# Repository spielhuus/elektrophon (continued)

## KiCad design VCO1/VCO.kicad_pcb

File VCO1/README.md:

# VCO1

This is a basic VCO designed by Thomas Henry. There are no special features, but it is a solid mixer.

Lorem ipsum dolor sit amet, consectetuer adipiscing elit. Aenean commodo ligula eget dolor. Aenean massa. Cum sociis natoque
penatibus et magnis dis parturient montes, nascetur ridiculus mus. Donec quam felis, ultricies nec, pellentesque eu, pretium quis, sem. Nulla consequat massa quis enim. Donec pede justo, fringilla vel, aliquet nec, vulputate eget, arcu. In enim justo, rhoncus ut, imperdiet a, venenatis vitae, justo. Nullam dictum felis eu pede mollis pretium. Integer tincidunt. Cras dapibus. Vivamus elementum semper nisi. Aenean vulputate eleifend tellus. Aenean leo ligula, porttitor eu, consequat vitae, eleifend ac, enim. Aliquam lorem ante, dapibus in, viverra quis, feugiat a, tellus. Phasellus viverra nulla ut metus varius laoreet. Quisque rutrum. Aenean imperdiet. Etiam ultricies nisi vel augue. Curabitur ullamcorper ultricies nisi. Nam eget dui. Etiam rhoncus. Maecenas tempus, tellus eget condimentum rhoncus, sem quam semper libero, sit amet adipiscing sem neque 

sed ipsum. Nam quam nunc, blandit vel, luctus pulvinar, hendrerit id, lorem. Maecenas nec odio et ante tincidunt tempus. Donec vitae sapien ut libero venenatis faucibus. Nullam quis ante. Etiam sit amet orci eget eros faucibus tincidunt. Duis leo. Sed fringilla mauris sit amet nibh. Donec sodales sagittis magna. Sed consequat, leo eget bibendum sodales, augue velit cursus nunc, Lorem ipsum dolor sit amet, consectetuer adipiscing elit. Aenean commodo ligula eget dolor. Aenean massa. Cum sociis natoque penatibus et magnis dis parturient montes, nascetur ridiculus mus. Donec quam felis, ultricies nec, pellentesque eu, pretium quis, sem. Nulla consequat massa quis enim. Donec pede justo, fringilla vel, aliquet nec, vulputate eget, arcu. In enim justo, rhoncus ut, imperdiet a, venenatis vitae, justo. Nullam dictum felis eu pede mollis pretium. Integer tincidunt. Cras dapibus. Vivamus elementum semper nisi. Aenean vulputate eleifend tellus. Aenean leo ligula, porttitor eu, consequat vitae, eleifend ac, enim. Aliquam lorem ante, dapibus in, viverra quis, feugiat a, tellus. Phasellus viverra nulla ut metus varius laoreet. Quisque rutrum. Aenean imperdiet. Etiam ultricies nisi vel augue. 

Curabitur ullamcorper ultricies nisi. Nam eget dui. Etiam rhoncus. Maecenas tempus, tellus eget condimentum rhoncus, sem quam semper libero, sit amet adipiscing sem neque sed ipsum. Nam quam nunc, blandit vel, luctus pulvinar, hendrerit id, lorem. Maecenas nec odio et ante tincidunt tempus. Donec vitae sapien ut libero venenatis faucibus. Nullam quis ante. Etiam sit amet orci eget eros faucibus tincidunt. Duis leo. Sed fringilla mauris sit amet nibh. Donec sodales sagittis magna. Sed consequat, leo eget bibendum sodales, augue velit cursus nunc - [BOM](BOM.csv) adipiscing sem neque sed ipsum. Nam quam nunc, blandit vel, luctus pulvinar, hendrerit id, lorem. Maecenas nec odio et ante tincidunt tempus. Donec vitae sapien ut libero venenatis faucibus. Nullam quis ante. Etiam sit amet orci eget eros faucibus tincidunt. Duis leo. Sed fringilla mauris sit amet nibh. Donec sodales sagittis magna. Sed consequat, leo eget bibendum sodales, augue velit cursus nun

## links

1) [Thomas Henry: VCO1](http://birthofasynth.com/Thomas_Henry/Pages/VCO-1.html)

---

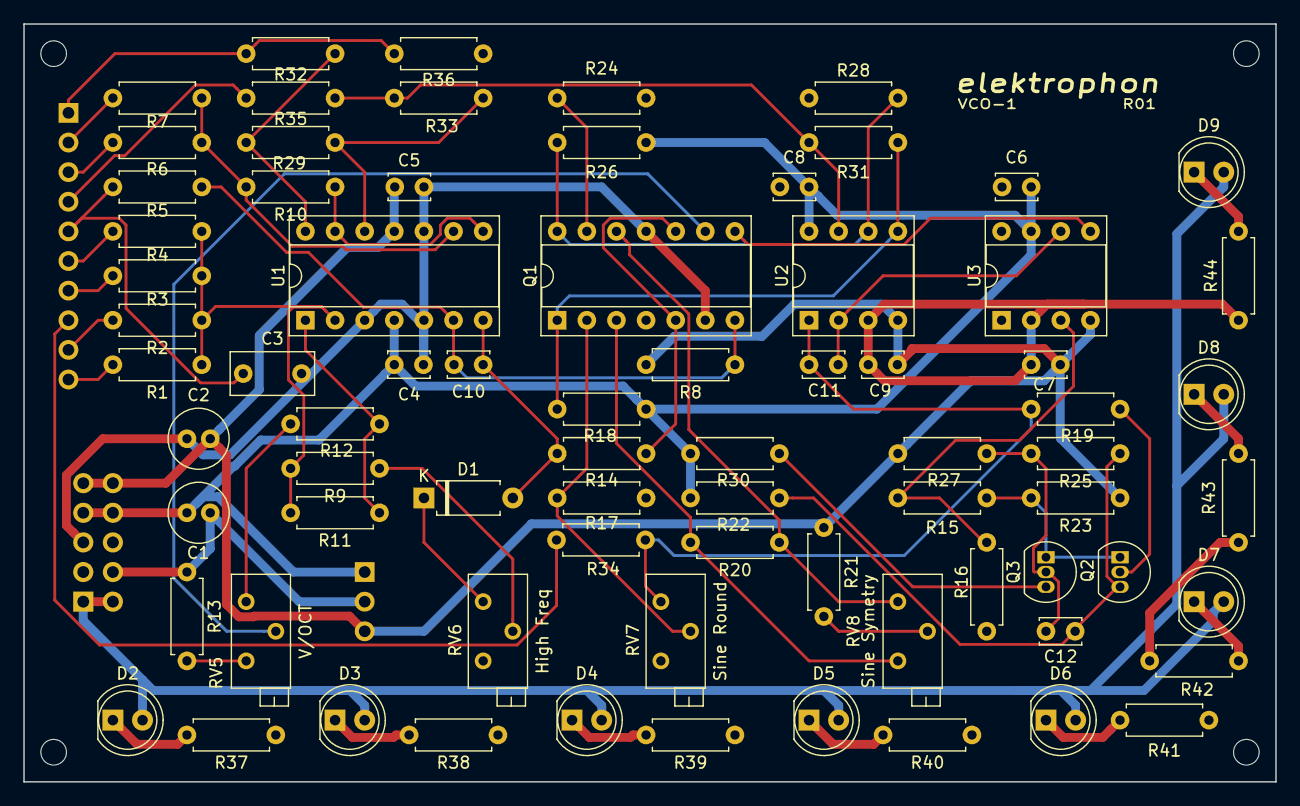
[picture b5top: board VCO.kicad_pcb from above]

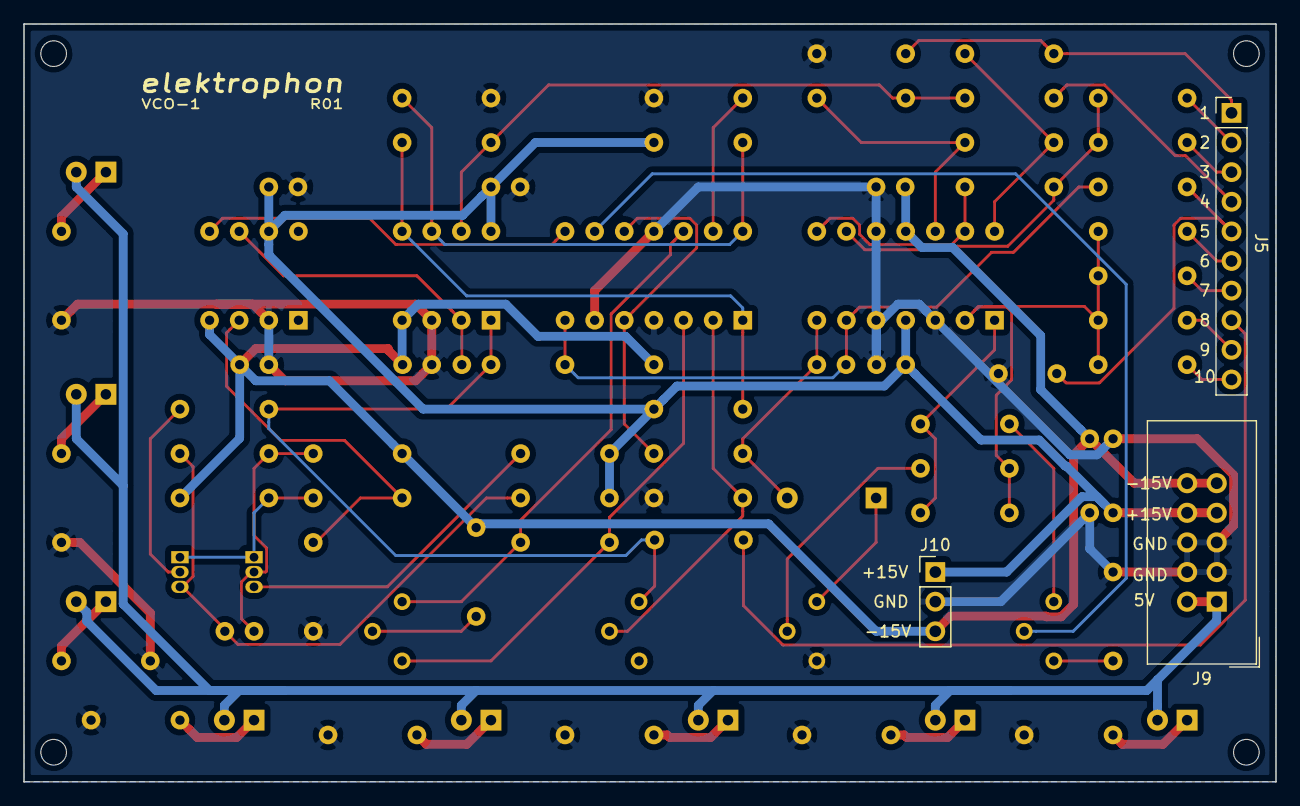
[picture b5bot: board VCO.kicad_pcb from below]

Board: 2 copper layers, 107.3 x 65.0 mm, 78 parts (3 on the bottom side), 53 nets.

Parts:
C1, C2: 10u; C_Radial_D5.0mm_H11.0mm_P2.00mm
C3: 0.22u; C_Rect_L7.0mm_W3.5mm_P5.00mm
C4, C5, C6, C7, C8, C9: 0.01u; C_Disc_D3.4mm_W2.1mm_P2.50mm
C10: 1n; C_Disc_D3.4mm_W2.1mm_P2.50mm
C11: 0.001u; C_Disc_D3.4mm_W2.1mm_P2.50mm
C12: 47p; C_Disc_D3.4mm_W2.1mm_P2.50mm
D1: D; D_A-405_P7.62mm_Horizontal
D2, D3, D4, D5, D6, D7, D8, D9: LED; LED_D5.0mm_FlatTop
J5: PANEL; PinHeader_1x10_P2.54mm_Vertical
J9: POWER; IDC-Header_2x05_P2.54mm_Vertical
J10: Panel Power; PinHeader_1x03_P2.54mm_Vertical
Q1: THAT340; DIP-14_W7.62mm_Socket
Q2, Q3: 2N3904; TO-92_Inline
R1, R2, R4, R6, R15, R27: 100k; R_Axial_DIN0207_L6.3mm_D2.5mm_P7.62mm_Horizontal
R3: 3M3; R_Axial_DIN0207_L6.3mm_D2.5mm_P7.62mm_Horizontal
R5: 1M; R_Axial_DIN0207_L6.3mm_D2.5mm_P7.62mm_Horizontal
R7: 330k; R_Axial_DIN0207_L6.3mm_D2.5mm_P7.62mm_Horizontal
R8: 1M5; R_Axial_DIN0207_L6.3mm_D2.5mm_P7.62mm_Horizontal
R9, R29: 2M2; R_Axial_DIN0207_L6.3mm_D2.5mm_P7.62mm_Horizontal
R10: 150k; R_Axial_DIN0207_L6.3mm_D2.5mm_P7.62mm_Horizontal
R11: 2k; R_Axial_DIN0207_L6.3mm_D2.5mm_P7.62mm_Horizontal
R12: 47; R_Axial_DIN0207_L6.3mm_D2.5mm_P7.62mm_Horizontal
R13: 820; R_Axial_DIN0207_L6.3mm_D2.5mm_P7.62mm_Horizontal
R14: 22k; R_Axial_DIN0207_L6.3mm_D2.5mm_P7.62mm_Horizontal
R16, R18, R22, R23, R24: 10k; R_Axial_DIN0207_L6.3mm_D2.5mm_P7.62mm_Horizontal
R17, R26, R28, R33: 2.2k; R_Axial_DIN0207_L6.3mm_D2.5mm_P7.62mm_Horizontal
R19: 27k; R_Axial_DIN0207_L6.3mm_D2.5mm_P7.62mm_Horizontal
R20: 390; R_Axial_DIN0207_L6.3mm_D2.5mm_P7.62mm_Horizontal
R21, R25: 18k; R_Axial_DIN0207_L6.3mm_D2.5mm_P7.62mm_Horizontal
R30: 5.1k; R_Axial_DIN0207_L6.3mm_D2.5mm_P7.62mm_Horizontal
R31: 12k; R_Axial_DIN0207_L6.3mm_D2.5mm_P7.62mm_Horizontal
R32, R36: 3k; R_Axial_DIN0207_L6.3mm_D2.5mm_P7.62mm_Horizontal
R34, R35, R37, R38, R39, R40, R41, R42, R43, R44: 1k; R_Axial_DIN0207_L6.3mm_D2.5mm_P7.62mm_Horizontal
RV5: 100 - V/OCT Trim; Potentiometer_Bourns_3296Z_Horizontal
RV6: 100k - High Freq Trim; Potentiometer_Bourns_3296Z_Horizontal
RV7: 100k - Sine Round Trim; Potentiometer_Bourns_3296Z_Horizontal
RV8: 50k - Sine Symetrie Trim; Potentiometer_Bourns_3296Z_Horizontal
U1: TL074; DIP-14_W7.62mm_Socket
U2: TL072; DIP-8_W7.62mm_Socket
U3: CA3080; DIP-8_W7.62mm_Socket

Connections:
+5V: D2.2, D3.2, D4.2, D5.2, D6.2, D7.2, D8.2, D9.2, J9.1, J9.2
+15V: C1.1, C4.1, C6.1, C8.1, J9.7, J9.8, J10.1, R18.2, R22.1, R24.2, R30.2, U1.4, U2.8, U3.7
-15V: C2.2, C5.2, C7.2, C9.2, J9.9, J9.10, J10.3, R8.2, R21.1, R23.1, R27.1, U1.11, U2.4, U3.4
/CV: J5.10, R1.2
/Coarse: J5.9, R2.2
/EXP_FM: J5.6, R4.2
/FINE: J5.7, R3.2
/INITIAL: J5.2, R7.2
/LIN_FM: C3.1, J5.5, R5.2
/PWM: J5.3, R6.2
/Pulse: J5.1, R32.1, R36.2
/Sine: J5.4, R35.1
/Triangle: J5.8, R34.1
GND: C1.2, C2.1, C3.2, C4.2, C5.1, C6.2, C7.1, C8.2, C9.1, J9.3, J9.4, J9.5, J9.6, J10.2, Q1.4, Q1.6, Q1.11, R13.1, R16.1, R17.1, R26.1, R28.1, R36.1, R37.1, R38.1, R39.1, R40.1, R41.1, R42.1, R43.1, R44.1, RV6.3, U1.3, U1.5, U1.10, U2.3, U3.2
unnamed: C10.1, D1.2, R14.1, U1.7
unnamed: C10.2, Q1.7, R5.1, R8.1, U1.6
unnamed: C11.1, R19.1, R34.2, RV7.1, U2.1
unnamed: C11.2, U2.2, U3.6
unnamed: C12.1, Q3.2, R25.2, R27.2
unnamed: C12.2, Q2.3, R22.2, R25.1
unnamed: D1.1, RV6.1
unnamed: D2.1, R37.2
unnamed: D3.1, R38.2
unnamed: D4.1, R39.2
unnamed: D5.1, R40.2
unnamed: D6.1, R41.2
unnamed: D7.1, R42.2
unnamed: D8.1, R43.2
unnamed: D9.1, R44.2
unnamed: Q1.1, R18.1, R31.2, U2.5
unnamed: Q1.2, R17.2, RV7.2
unnamed: Q1.3, R20.2, RV8.3
unnamed: Q1.8, U3.5
unnamed: Q1.9, RV5.2
unnamed: Q1.5, Q1.10, R14.2
unnamed: Q1.12, R20.1, RV8.1
unnamed: Q1.13, R26.2
unnamed: Q1.14, R24.1, R28.2, U2.6
unnamed: Q2.1, Q3.1, R15.2, R23.2
unnamed: Q2.2, R19.2
unnamed: Q3.3, R30.1
unnamed: R1.1, R2.1, R3.1, R4.1, R9.2, R11.2, U1.2
unnamed: R9.1, RV6.2
unnamed: R10.1, U1.8, U1.13
unnamed: R6.1, R7.1, R10.2, U1.9
unnamed: R11.1, R12.2, U1.1
unnamed: R12.1, RV5.1
unnamed: R13.2, RV5.3
unnamed: R15.1, R16.2, U3.3
unnamed: R21.2, RV8.2
unnamed: R29.1, R32.2, U1.14
unnamed: R29.2, R33.1, U1.12
unnamed: R31.1, R33.2, R35.2, U2.7

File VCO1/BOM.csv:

Reference, Quantity, Value, Footprint, Datasheet
C10 ,1,"1n","Capacitor_THT:C_Disc_D3.4mm_W2.1mm_P2.50mm","~"
C11 ,1,"0.001u","Capacitor_THT:C_Disc_D3.4mm_W2.1mm_P2.50mm","~"
C12 ,1,"47p","Capacitor_THT:C_Disc_D3.4mm_W2.1mm_P2.50mm","~"
C2 C1 ,2,"10u","Capacitor_THT:C_Radial_D5.0mm_H11.0mm_P2.00mm","~"
C3 ,1,"0.22u","Capacitor_THT:C_Rect_L7.0mm_W3.5mm_P5.00mm","~"
C4 C7 C6 C5 C8 C9 ,6,"0.01u","Capacitor_THT:C_Disc_D3.4mm_W2.1mm_P2.50mm","~"
D1 ,1,"D","Diode_THT:D_A-405_P7.62mm_Horizontal","~"
D6 D7 D8 D9 D5 D4 D3 D2 ,8,"LED","LED_THT:LED_D5.0mm_FlatTop","~"
J1 ,1,"EXP FM","Connector:Banana_Jack_1Pin","~"
J10 ,1,"Panel Power","Connector_PinHeader_2.54mm:PinHeader_1x03_P2.54mm_Vertical","~"
J2 ,1,"LIN FM","Connector:Banana_Jack_1Pin","~"
J3 ,1,"CV (1V/OCT)","Connector:Banana_Jack_1Pin","~"
J4 ,1,"PWM","Connector:Banana_Jack_1Pin","~"
J5 ,1,"PANEL","Connector_PinHeader_2.54mm:PinHeader_1x10_P2.54mm_Vertical","~"
J6 ,1,"Triangle","Connector:Banana_Jack_1Pin","~"
J7 ,1,"Sine","Connector:Banana_Jack_1Pin","~"
J8 ,1,"Pulse","Connector:Banana_Jack_1Pin","~"
J9 ,1,"POWER","Connector_IDC:IDC-Header_2x05_P2.54mm_Vertical","~"
Q1 ,1,"THAT340","Package_DIP:DIP-14_W7.62mm_Socket",""
Q2 Q3 ,2,"2N3904","Package_TO_SOT_THT:TO-92_Inline","https://www.fairchildsemi.com/datasheets/2N/2N3904.pdf"
R1 R4 R2 R15 R27 R6 ,6,"100k","Resistor_THT:R_Axial_DIN0207_L6.3mm_D2.5mm_P7.62mm_Horizontal","~"
R10 ,1,"150k","Resistor_THT:R_Axial_DIN0207_L6.3mm_D2.5mm_P7.62mm_Horizontal","~"
R11 ,1,"2k","Resistor_THT:R_Axial_DIN0207_L6.3mm_D2.5mm_P7.62mm_Horizontal","~"
R12 ,1,"47","Resistor_THT:R_Axial_DIN0207_L6.3mm_D2.5mm_P7.62mm_Horizontal","~"
R13 ,1,"820","Resistor_THT:R_Axial_DIN0207_L6.3mm_D2.5mm_P7.62mm_Horizontal","~"
R14 ,1,"22k","Resistor_THT:R_Axial_DIN0207_L6.3mm_D2.5mm_P7.62mm_Horizontal","~"
R16 R23 R22 R18 R24 ,5,"10k","Resistor_THT:R_Axial_DIN0207_L6.3mm_D2.5mm_P7.62mm_Horizontal","~"
R17 R26 R28 R33 ,4,"2.2k","Resistor_THT:R_Axial_DIN0207_L6.3mm_D2.5mm_P7.62mm_Horizontal","~"
R19 ,1,"27k","Resistor_THT:R_Axial_DIN0207_L6.3mm_D2.5mm_P7.62mm_Horizontal","~"
R20 ,1,"390","Resistor_THT:R_Axial_DIN0207_L6.3mm_D2.5mm_P7.62mm_Horizontal","~"
R25 R21 ,2,"18k","Resistor_THT:R_Axial_DIN0207_L6.3mm_D2.5mm_P7.62mm_Horizontal","~"
R3 ,1,"3M3","Resistor_THT:R_Axial_DIN0207_L6.3mm_D2.5mm_P7.62mm_Horizontal","~"
R30 ,1,"5.1k","Resistor_THT:R_Axial_DIN0207_L6.3mm_D2.5mm_P7.62mm_Horizontal","~"
R31 ,1,"12k","Resistor_THT:R_Axial_DIN0207_L6.3mm_D2.5mm_P7.62mm_Horizontal","~"
R32 R36 ,2,"3k","Resistor_THT:R_Axial_DIN0207_L6.3mm_D2.5mm_P7.62mm_Horizontal","~"
R34 R35 R37 R38 R39 R40 R41 R42 R43 R44 ,10,"1k","Resistor_THT:R_Axial_DIN0207_L6.3mm_D2.5mm_P7.62mm_Horizontal","~"
R5 ,1,"1M","Resistor_THT:R_Axial_DIN0207_L6.3mm_D2.5mm_P7.62mm_Horizontal","~"
R7 ,1,"330k","Resistor_THT:R_Axial_DIN0207_L6.3mm_D2.5mm_P7.62mm_Horizontal","~"
R8 ,1,"1M5","Resistor_THT:R_Axial_DIN0207_L6.3mm_D2.5mm_P7.62mm_Horizontal","~"
R9 R29 ,2,"2M2","Resistor_THT:R_Axial_DIN0207_L6.3mm_D2.5mm_P7.62mm_Horizontal","~"
RV1 RV2 RV3 RV4 ,4,"100k","Resistor_THT:R_Axial_DIN0207_L6.3mm_D2.5mm_P10.16mm_Horizontal","~"
RV5 ,1,"100 - V/OCT Trim","Potentiometer_THT:Potentiometer_Bourns_3296Z_Horizontal","~"
RV6 ,1,"100k - High Freq Trim","Potentiometer_THT:Potentiometer_Bourns_3296Z_Horizontal","~"
RV7 ,1,"100k - Sine Round Trim","Potentiometer_THT:Potentiometer_Bourns_3296Z_Horizontal","~"
RV8 ,1,"50k - Sine Symetrie Trim","Potentiometer_THT:Potentiometer_Bourns_3296Z_Horizontal","~"
U1 ,1,"TL074","Package_DIP:DIP-14_W7.62mm_Socket","http://www.ti.com/lit/ds/symlink/tl071.pdf"
U2 ,1,"TL072","Package_DIP:DIP-8_W7.62mm_Socket","http://www.ti.com/lit/ds/symlink/tl071.pdf"
U3 ,1,"CA3080","Package_DIP:DIP-8_W7.62mm_Socket","http://www.intersil.com/content/dam/Intersil/documents/ca30/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"

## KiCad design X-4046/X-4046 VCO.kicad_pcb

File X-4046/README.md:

# X-4046 VCO

This is a basic VCO designed by Thomas Henry. There are no special features, but it is a solid mixer.

Lorem ipsum dolor sit amet, consectetuer adipiscing elit. Aenean commodo ligula eget dolor. Aenean massa. Cum sociis natoque
penatibus et magnis dis parturient montes, nascetur ridiculus mus. Donec quam felis, ultricies nec, pellentesque eu, pretium quis, sem. Nulla consequat massa quis enim. Donec pede justo, fringilla vel, aliquet nec, vulputate eget, arcu. In enim justo, rhoncus ut, imperdiet a, venenatis vitae, justo. Nullam dictum felis eu pede mollis pretium. Integer tincidunt. Cras dapibus. Vivamus elementum semper nisi. Aenean vulputate eleifend tellus. Aenean leo ligula, porttitor eu, consequat vitae, eleifend ac, enim. Aliquam lorem ante, dapibus in, viverra quis, feugiat a, tellus. Phasellus viverra nulla ut metus varius laoreet. Quisque rutrum. Aenean imperdiet. Etiam ultricies nisi vel augue. Curabitur ullamcorper ultricies nisi. Nam eget dui. Etiam rhoncus. Maecenas tempus, tellus eget condimentum rhoncus, sem quam semper libero, sit amet adipiscing sem neque 

sed ipsum. Nam quam nunc, blandit vel, luctus pulvinar, hendrerit id, lorem. Maecenas nec odio et ante tincidunt tempus. Donec vitae sapien ut libero venenatis faucibus. Nullam quis ante. Etiam sit amet orci eget eros faucibus tincidunt. Duis leo. Sed fringilla mauris sit amet nibh. Donec sodales sagittis magna. Sed consequat, leo eget bibendum sodales, augue velit cursus nunc, Lorem ipsum dolor sit amet, consectetuer adipiscing elit. Aenean commodo ligula eget dolor. Aenean massa. Cum sociis natoque penatibus et magnis dis parturient montes, nascetur ridiculus mus. Donec quam felis, ultricies nec, pellentesque eu, pretium quis, sem. Nulla consequat massa quis enim. Donec pede justo, fringilla vel, aliquet nec, vulputate eget, arcu. In enim justo, rhoncus ut, imperdiet a, venenatis vitae, justo. Nullam dictum felis eu pede mollis pretium. Integer tincidunt. Cras dapibus. Vivamus elementum semper nisi. Aenean vulputate eleifend tellus. Aenean leo ligula, porttitor eu, consequat vitae, eleifend ac, enim. Aliquam lorem ante, dapibus in, viverra quis, feugiat a, tellus. Phasellus viverra nulla ut metus varius laoreet. Quisque rutrum. Aenean imperdiet. Etiam ultricies nisi vel augue. 

Curabitur ullamcorper ultricies nisi. Nam eget dui. Etiam rhoncus. Maecenas tempus, tellus eget condimentum rhoncus, sem quam semper libero, sit amet adipiscing sem neque sed ipsum. Nam quam nunc, blandit vel, luctus pulvinar, hendrerit id, lorem. Maecenas nec odio et ante tincidunt tempus. Donec vitae sapien ut libero venenatis faucibus. Nullam quis ante. Etiam sit amet orci eget eros faucibus tincidunt. Duis leo. Sed fringilla mauris sit amet nibh. Donec sodales sagittis magna. Sed consequat, leo eget bibendum sodales, augue velit cursus nunc - [BOM](BOM.csv) adipiscing sem neque sed ipsum. Nam quam nunc, blandit vel, luctus pulvinar, hendrerit id, lorem. Maecenas nec odio et ante tincidunt tempus. Donec vitae sapien ut libero venenatis faucibus. Nullam quis ante. Etiam sit amet orci eget eros faucibus tincidunt. Duis leo. Sed fringilla mauris sit amet nibh. Donec sodales sagittis magna. Sed consequat, leo eget bibendum sodales, augue velit cursus nun

## links

1) [Thomas Henry: X-4046](http://birthofasynth.com/Thomas_Henry/Pages/X-4046.html)

---

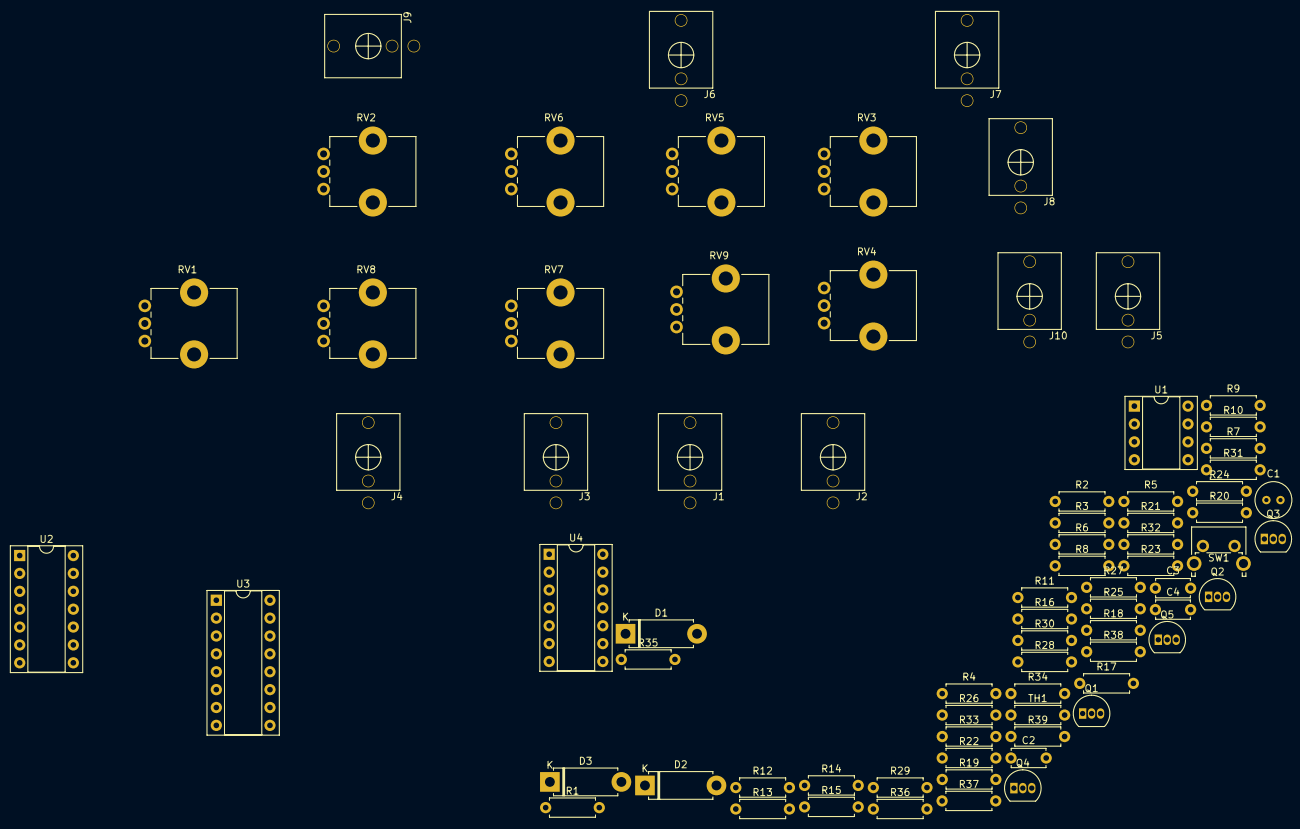
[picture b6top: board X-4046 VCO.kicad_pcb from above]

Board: 2 copper layers, 76 parts (0 on the bottom side), 57 nets, no tracks yet.

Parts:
C1: 100pF; C_Radial_D5.0mm_H5.0mm_P2.00mm
C2: 0.01u; C_Disc_D4.7mm_W2.5mm_P5.00mm
C3: 0.22u; C_Disc_D4.7mm_W2.5mm_P5.00mm
C4: 470p; C_Disc_D4.7mm_W2.5mm_P5.00mm
D1, D2, D3: D; D_5W_P10.16mm_Horizontal
J1: Linear FM; PJ301M-12
J2: Hard Sync; PJ301M-12
J3: EXP FM; PJ301M-12
J4: 1V/OCT; PJ301M-12
J5: PWM; PJ301M-12
J6: Triangle; PJ301M-12
J7: RAMPOID; PJ301M-12
J8: PJ301M-12
J9: SINE; PJ301M-12
J10: PULSE; PJ301M-12
Q1, Q2, Q3, Q4, Q5: 2N3904; TO-92_Inline
R1: 1M5; R_Axial_DIN0207_L6.3mm_D2.5mm_P7.62mm_Horizontal
R2, R3, R4, R10, R13, R15, R16, R27, R31: 100k; R_Axial_DIN0207_L6.3mm_D2.5mm_P7.62mm_Horizontal
R5: 3M3; R_Axial_DIN0207_L6.3mm_D2.5mm_P7.62mm_Horizontal
R6: 12k; R_Axial_DIN0207_L6.3mm_D2.5mm_P7.62mm_Horizontal
R7, R19, R20, R24, R28, R29: 10k; R_Axial_DIN0207_L6.3mm_D2.5mm_P7.62mm_Horizontal
R8: 33k; R_Axial_DIN0207_L6.3mm_D2.5mm_P7.62mm_Horizontal
R9, R22, R23: 75k; R_Axial_DIN0207_L6.3mm_D2.5mm_P7.62mm_Horizontal
R11, R25: 220k; R_Axial_DIN0207_L6.3mm_D2.5mm_P7.62mm_Horizontal
R12, R34: 120k; R_Axial_DIN0207_L6.3mm_D2.5mm_P7.62mm_Horizontal
R14, R35, R36, R39: 1k; R_Axial_DIN0207_L6.3mm_D2.5mm_P7.62mm_Horizontal
R17, R21: 390; R_Axial_DIN0207_L6.3mm_D2.5mm_P7.62mm_Horizontal
R18: 4k7; R_Axial_DIN0207_L6.3mm_D2.5mm_P7.62mm_Horizontal
R26, R30: 2.2k; R_Axial_DIN0207_L6.3mm_D2.5mm_P7.62mm_Horizontal
R32: 330k; R_Axial_DIN0207_L6.3mm_D2.5mm_P7.62mm_Horizontal
R33: 2.2M; R_Axial_DIN0207_L6.3mm_D2.5mm_P7.62mm_Horizontal
R37: 3k; R_Axial_DIN0207_L6.3mm_D2.5mm_P7.62mm_Horizontal
R38: 1.8k; R_Axial_DIN0207_L6.3mm_D2.5mm_P7.62mm_Horizontal
RV1, RV2, RV3, RV5, RV6, RV7, RV8, RV9: 100k; Potentiometer_Bourns_PTV09A-1_Single_Vertical
RV4: 100 (TRIM); Potentiometer_Bourns_PTV09A-1_Single_Vertical
SW1: AC/DC Switch; SW_Tactile_SPST_Angled_PTS645Vx31-2LFS
TH1: 2k +3500ppm/°C; R_Axial_DIN0207_L6.3mm_D2.5mm_P7.62mm_Horizontal
U1: LF442; DIP-8_W7.62mm_Socket
U2, U4: TL074; DIP-14_W7.62mm_Socket
U3: 4046; DIP-16_W7.62mm_Socket

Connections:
+15V: R1.2, R18.2, R20.2, R24.2, RV2.1, RV3.1, RV8.3, U3.9, U3.14, U3.16
-15V: RV2.3, RV3.3
/CI_1: C2.1, U2.5, U3.6
/CI_2: C2.2, U2.3, U3.7
/Demodulator_OUT: Q2.3, U3.11
/VCO_OUT: RV6.1, U3.4
/sigin: Q3.3, R18.1, U3.3
GND: D3.2, J8.1, Q2.2, Q3.1, R12.1, R17.1, R19.1, R26.1, R28.1, R38.1, RV1.3, RV7.3, RV8.1, RV9.3, U1.3, U1.5, U2.13, U3.8, U4.13
unnamed: C1.1, R6.1, RV5.1, U1.7
unnamed: C1.2, Q1.3, R1.1, R15.1, U1.6
unnamed: C3.1, RV9.1, SW1.2
unnamed: C3.2, J1.1, SW1.1
unnamed: C4.1, R16.2
unnamed: C4.2, J2.1
unnamed: D1.1, D2.2
unnamed: D1.2, Q1.2, RV4.2
unnamed: D2.1, R7.2
unnamed: D3.1, Q3.2, R16.1
unnamed: J3.1, RV1.1
unnamed: J4.1, R2.2
unnamed: J6.1, R14.2
unnamed: J7.1, R36.1
unnamed: J8.3, R35.1
unnamed: J9.1, R39.1
unnamed: J10.1, R37.1, R38.2
unnamed: Q1.1, Q2.1, R6.2
unnamed: Q4.1, R21.2
unnamed: Q4.2, R19.2
unnamed: Q4.3, R20.1, R29.2, U4.6
unnamed: Q5.1, R21.1
unnamed: Q5.2, R26.2
unnamed: Q5.3, R24.1, R28.2, U4.5
unnamed: R2.1, R3.1, R4.1, R5.1, TH1.2, U1.2
unnamed: R3.2, RV1.2
unnamed: R4.2, RV2.2
unnamed: R5.2, RV3.2
unnamed: R7.1, RV5.2
unnamed: R8.1, RV7.2
unnamed: R10.1, RV6.2
unnamed: R10.2, R12.2, U2.9
unnamed: R8.2, R9.2, R11.1, R13.1, U2.10
unnamed: R11.2, RV8.2
unnamed: R13.2, R14.1, U2.8
unnamed: R15.2, RV9.2
unnamed: R17.2, RV4.3
unnamed: R22.1, R23.1, R25.1, R27.2, U2.12
unnamed: R22.2, RV7.1, U2.1, U2.2
unnamed: R9.1, R23.2, U2.6, U2.7
unnamed: R27.1, R35.2, U2.14
unnamed: R29.1, R30.2, R39.2, U4.7
unnamed: R30.1, R33.2, U4.10
unnamed: R31.1, R32.1, R34.2, U4.12
unnamed: R33.1, R37.2, U4.8
unnamed: R34.1, U4.9, U4.14
unnamed: R36.2, U4.1, U4.2
unnamed: RV4.1, TH1.1
unnamed: U3.2, U3.5

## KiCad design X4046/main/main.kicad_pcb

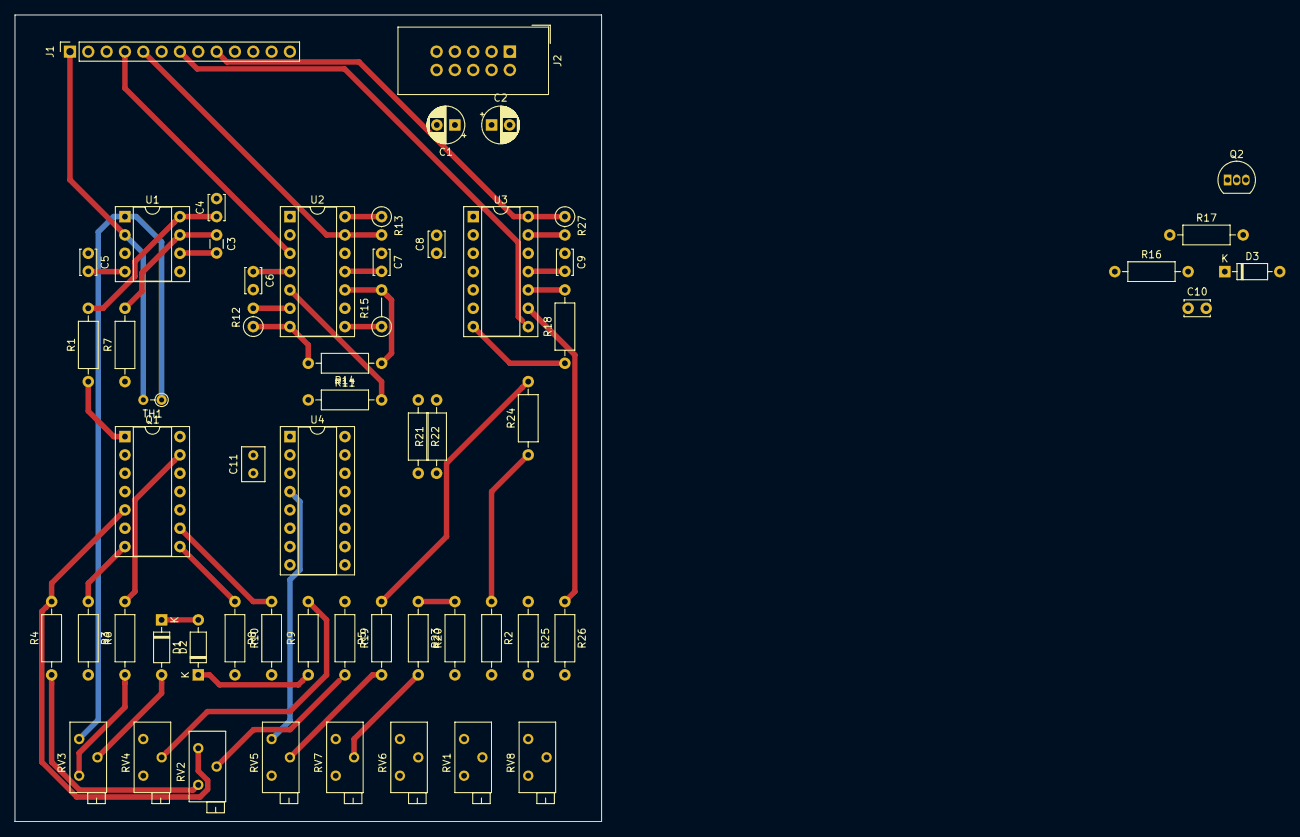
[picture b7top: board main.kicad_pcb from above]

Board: 2 copper layers, 81.3 x 111.8 mm, 58 parts (0 on the bottom side), 48 nets.

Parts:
C1, C2: 10u; CP_Radial_D5.0mm_P2.50mm
C3: 100p; C_Disc_D3.0mm_W1.6mm_P2.50mm
C4, C5, C6, C7, C8, C9: 0.1u; C_Disc_D3.4mm_W2.1mm_P2.50mm
C10: 470p; C_Disc_D3.4mm_W2.1mm_P2.50mm
C11: 0.01u (Mylar); C_Rect_L4.6mm_W3.0mm_P2.50mm_MKS02_FKP02
D1, D2, D3: 1N4148; D_DO-35_SOD27_P7.62mm_Horizontal
J1: Conn_01x13_Female; PinSocket_1x13_P2.54mm_Vertical
J2: IDC Header; IDC-Header_2x05_P2.54mm_Vertical
Q1: THAT300; DIP-14_W7.62mm_Socket
Q2: 2N3904; TO-92_Inline
R1: 1M5; R_Axial_DIN0207_L6.3mm_D2.5mm_P10.16mm_Horizontal
R2: 2k2; R_Axial_DIN0207_L6.3mm_D2.5mm_P10.16mm_Horizontal
R3, R8, R9, R11: 10k; R_Axial_DIN0207_L6.3mm_D2.5mm_P10.16mm_Horizontal
R4, R6: 390; R_Axial_DIN0207_L6.3mm_D2.5mm_P10.16mm_Horizontal
R5: 18k; R_Axial_DIN0207_L6.3mm_D2.5mm_P10.16mm_Horizontal
R7: 12k; R_Axial_DIN0207_L6.3mm_D2.5mm_P10.16mm_Horizontal
R10, R14: 2.2k; R_Axial_DIN0207_L6.3mm_D2.5mm_P10.16mm_Horizontal
R12: 10k; R_Axial_DIN0207_L6.3mm_D2.5mm_P2.54mm_Vertical
R13: 120k; R_Axial_DIN0207_L6.3mm_D2.5mm_P2.54mm_Vertical
R15: 2.2M; R_Axial_DIN0207_L6.3mm_D2.5mm_P5.08mm_Vertical
R16, R19, R26: 100k; R_Axial_DIN0207_L6.3mm_D2.5mm_P10.16mm_Horizontal
R17: 4k7; R_Axial_DIN0207_L6.3mm_D2.5mm_P10.16mm_Horizontal
R18, R21, R22: 75k; R_Axial_DIN0207_L6.3mm_D2.5mm_P10.16mm_Horizontal
R20: 33k; R_Axial_DIN0207_L6.3mm_D2.5mm_P10.16mm_Horizontal
R23, R25: 220k; R_Axial_DIN0207_L6.3mm_D2.5mm_P10.16mm_Horizontal
R24: 120k; R_Axial_DIN0207_L6.3mm_D2.5mm_P10.16mm_Horizontal
R27: 100k; R_Axial_DIN0207_L6.3mm_D2.5mm_P2.54mm_Vertical
RV1, RV4, RV5, RV6, RV7: 100k; Potentiometer_Bourns_3296Z_Horizontal
RV2: 50k; Potentiometer_Bourns_3296Z_Horizontal
RV3: 100; Potentiometer_Bourns_3296Z_Horizontal
RV8: 100k (TRIM); Potentiometer_Bourns_3296Z_Horizontal
TH1: 2k +3500ppm/°C PTC; R_Axial_DIN0204_L3.6mm_D1.6mm_P2.54mm_Vertical
U1: LF442; DIP-8_W7.62mm_Socket
U2, U3: TL074; DIP-14_W7.62mm_Socket
U4: 4046; DIP-16_W7.62mm_Socket

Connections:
+5V: J2.9, J2.10
+15V: C1.1, C4.1, C6.1, C8.1, J1.11, J2.3, J2.4, R1.2, R3.2, R8.2, R17.1, RV7.3, U1.8, U2.4, U3.4, U4.9, U4.14, U4.16
-15V: C2.2, C5.2, C7.2, C9.2, J1.12, J2.1, J2.2, R5.1, RV8.3, U1.4, U2.11, U3.11
/CI_1: C11.2, U3.5, U4.6
/CI_2: C11.1, U3.3, U4.7
/CV: Q1.14, U4.11
/EXP_FM: J1.1, TH1.2, U1.2
/HARD_SYNC: C10.2, J1.3
/LIN_FM: C3.2, J1.2, Q1.1, R1.1, U1.6
/PULSE: J1.10, R15.1, U2.8
/PWM: J1.5, R13.2, U2.13
/RAMPOID: J1.8, U2.1, U2.2
/SAW: J1.9, R27.1, U3.14
/SINE: J1.6, R12.1, R14.2, U2.7
/SKEW: J1.4, U2.3
/SYNC: Q2.3, R17.2, U4.3
/TRIANGLE: J1.7, R26.2, RV1.2, U3.8
/VCO_OUT: RV5.1, U4.4
GND: C1.2, C2.1, C4.2, C5.1, C6.2, C7.1, C8.2, C9.1, D3.2, J1.13, J2.5, J2.6, J2.7, J2.8, Q1.13, Q2.1, R2.1, R6.2, R10.1, R11.1, R24.1, RV5.3, RV6.3, RV7.1, RV8.1, U1.3, U1.5, U2.12, U3.12, U4.8
unnamed: C3.1, R7.2, RV4.1, U1.7
unnamed: C10.1, R16.2
unnamed: D1.1, D2.2
unnamed: D1.2, Q1.2, RV3.2
unnamed: D2.1, R9.1
unnamed: D3.1, Q2.2, R16.1
unnamed: Q1.5, R4.2, RV2.1
unnamed: Q1.6, R2.2, RV1.1
unnamed: Q1.7, R3.1, R12.2, U2.6
unnamed: Q1.8, R8.1, R11.2, U2.5
unnamed: Q1.9, R10.2
unnamed: Q1.10, R4.1, RV2.3
unnamed: Q1.3, Q1.12, R7.1
unnamed: R5.2, RV2.2
unnamed: R6.1, RV3.3
unnamed: R9.2, RV4.2
unnamed: R13.1, U2.9, U2.14
unnamed: R14.1, R15.2, U2.10
unnamed: R18.1, R22.2, U3.6, U3.7
unnamed: R18.2, R19.2, R24.2, U3.10
unnamed: R19.1, RV5.2
unnamed: R20.1, RV6.2
unnamed: R20.2, R23.1, R26.1, U3.9
unnamed: R21.1, R22.1, R25.1, R27.2, U3.13
unnamed: R21.2, RV6.1, U3.1, U3.2
unnamed: R23.2, RV7.2
unnamed: R25.2, RV8.2
unnamed: RV3.1, TH1.1, U1.1
unnamed: U4.2, U4.5
